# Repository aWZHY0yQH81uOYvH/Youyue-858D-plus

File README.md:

Youyue-858D-plus
================

Custom firmware and adapter PCB for the Youyue 858D+ with MK1841D3 stock MCU

This board and firmware is designed only for the ATmega328*PB* because it makes use of its extra port E I/O.

This repo includes a PCB that contains all the mods I could find:
* wguibas's MK1841D3 to AVR pinout adapting
* madworm's fancy fan speed commutation sensing
* RaiHei's buzzer
* Gabse's max fan speed cooldown
* 4 buttons for recalling preset temperatures
* Some extra I/O breakout for more hacking

Order the parts and PCB in the PCB folder. Then, use [this instructable](https://www.instructables.com/id/858D-SMD-Hot-Ait-Reflow-Station-Hack/) as a general guide. Add some buttons to the front panel for the presets.

There is a 'user manual' of sorts in the 'Docs' folder.

Some videos showing the progress from 'stock firmware' with massive temperature overshoot
towards almost no overshoot at all.

https://www.youtube.com/playlist?list=PLONcxJMOrdyeYuEgM6qhCllZelN6gPjrT

Please note:

Although this device looks very much like ones sold by 'Atten' and others, the innards
are not necessarily the same. The heater / wand are probably the same, but I know that
e.g. the 'Atten 858D' uses a different mainboard with a different brand microcontroller.

Naturally, this firmware will only work 'as is' for the exact mcu / mainboard combination I have.
Please see the 'Docs' folder for schematic and PCB photos.

Compiling/Development
=====================
Since this version of the firmware uses the PB variant of the chip, you need to use the makefile. You may need to adjust `ISP_PROG` and `AVRDUDE_ARD_PROGRAMMER` in the makefile depending on what programmer you have.
* Do `make` to just compile the project.
* Do `make ispload` to compile and upload the project.
* If you don't want to edit the firmware, you can just follow the instructions in the binaries folder to upload without compiling.

---

Safety information / disclaimer:
================================

Making any modifications to this device may cause you irreversible physical harm or worse.
You do this at your own risk. 

There is a significant risk of lethal electrical shock, so if you still insist of doing so, make sure to
ALWAYS UNPLUG THE MAINS CABLE before dismantling the device. Check repeatedly.

If you have an isolation transformer - do use it.

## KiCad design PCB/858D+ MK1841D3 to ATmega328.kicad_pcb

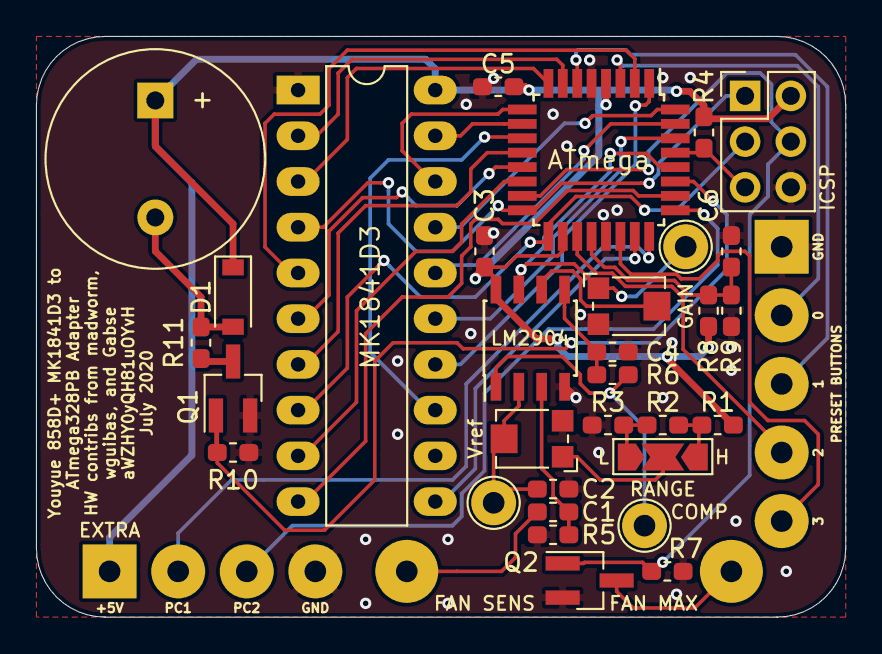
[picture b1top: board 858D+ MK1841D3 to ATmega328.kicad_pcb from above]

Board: 2 copper layers, 45.0 x 32.3 mm, 35 parts (0 on the bottom side), 42 nets.

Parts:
BZ1: Buzzer; Buzzer_12x9.5RM6.5
C1, C2, C3, C5, C6: 100n; C_0603_1608Metric_Pad1.05x0.95mm_HandSolder
C4: 1µ; C_0603_1608Metric_Pad1.05x0.95mm_HandSolder
D1: D_Small; D_SOD-123
J1: ISENSE; SolderWirePad_1x01_Drill1.2mm
J2: ICSP; PinHeader_2x03_P2.54mm_Vertical
J3: MK1841D3; DIP-20_W7.62mm_LongPads
J4: Extra; SolderWirePad_1x04_P3.81mm_Drill1.2mm
J5: FAN_MAX_SPEED; SolderWirePad_1x01_Drill1.2mm
JP1: SolderJumper_3_Open; SolderJumper-3_P2.0mm_Open_TrianglePad1.0x1.5mm
Q1, Q2: 2N7002; SOT-23_Handsoldering
R1, R4, R7, R8, R9, R10: 10k; R_0603_1608Metric_Pad1.05x0.95mm_HandSolder
R2, R3: 390; R_0603_1608Metric_Pad1.05x0.95mm_HandSolder
R5: 1M; R_0603_1608Metric_Pad1.05x0.95mm_HandSolder
R6: 100k; R_0603_1608Metric_Pad1.05x0.95mm_HandSolder
R11: 220; R_0603_1608Metric_Pad1.05x0.95mm_HandSolder
RV1, RV2: 10k; Potentiometer_Bourns_TC33X_Vertical
SW1: SW_Push_4x; SolderWirePad_1x05_P3.81mm_Drill1.2mm
TP1: Vref; TestPoint_THTPad_D2.5mm_Drill1.2mm
TP2: COMP_ADJ; TestPoint_THTPad_D2.5mm_Drill1.2mm
TP3: FAN_SPEED; TestPoint_THTPad_D2.5mm_Drill1.2mm
U1: LM2904; SOIC-8_3.9x4.9mm_P1.27mm
U2: ATmega328PB-AU; TQFP-32_7x7mm_P0.8mm

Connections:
+5V: BZ1.1, C3.1, C5.2, D1.1, J2.2, J3.20, J4.1, R1.1, R4.1, R8.1, U1.8, U2.4, U2.18
/PB0: J3.7, U2.12
/PB1: J3.6, U2.13
/PB2: J3.9, U2.14
/PB3: J2.4, Q2.1, R7.1, U2.15
/PB4: J2.1, J3.4, U2.16
/PB5: J2.3, J3.8, U2.17
/PB6: J3.2, U2.7
/PB7: J3.3, U2.8
/PC0: J3.11, U2.23
/PC1: J4.2, U2.24
/PC2: J4.3, U2.25
/PC3: J3.10, U2.26
/PC4: Q1.1, R10.1, U2.27
/PC5: RV2.1, TP3.1, U1.7, U2.28
/PD0: J3.15, U2.30
/PD1: J3.16, U2.31
/PD2: J3.17, U2.32
/PD3: J3.14, U2.1
/PD4: J3.5, U2.2
/PD5: J3.18, U2.9
/PD6: J3.19, U2.10
/PD7: J3.13, U2.11
/PE0: SW1.2, U2.3
/PE1: SW1.3, U2.6
/PE2: SW1.4, U2.19
/PE3: SW1.5, U2.22
/RESET: J2.5, R4.2, U2.29
GND: C2.2, C3.2, C4.2, C5.1, C6.2, J2.6, J3.1, J4.4, Q1.2, Q2.2, R3.2, R5.2, R7.2, R9.2, R10.2, RV1.3, RV2.3, SW1.1, U1.4, U2.5, U2.21
unnamed: BZ1.2, D1.2, R11.1
unnamed: C1.1, R5.1, U1.3
unnamed: C1.2, J1.1
unnamed: C2.1, RV1.2, TP1.1, U1.2
unnamed: C4.1, R6.1, U1.5
unnamed: C6.1, R8.2, R9.1, U2.20
unnamed: J5.1, Q2.3
unnamed: JP1.1, R2.2, R3.1
unnamed: JP1.2, RV1.1
unnamed: JP1.3, R1.2, R2.1
unnamed: Q1.3, R11.2
unnamed: R6.2, TP2.1, U1.1
unnamed: RV2.2, U1.6

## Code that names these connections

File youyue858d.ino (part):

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#define FW_MINOR_V_A 4
#define FW_MINOR_V_B 9
/*
 * PC5: FAN-speed (A5 in Arduino lingo) (OK)
 * PC3: TIP122.base --> FAN (OK)
 * PC2: fan-current-sense mod (OPTIONAL) - see Docs folder
 * PC0: ADC <-- amplif. thermo couple voltage (A0 in Arduino lingo) (OK)
 * #21: AREF <--- about 2.5V as analog reference for ADC
 * PB1: opto-triac driver !! THIS IS DANGEROUS TO USE !! (OK)
 * PB3: FAN to maximum output (OPTIONAL)
 *
 * PB0: 7-seg digit 0 [common Anode] (OK) 
 * PB7: 7-seg digit 1 [common Anode] (OK)
 * PB6: 7-seg digit 2 [common Anode] (OK)
 *
 * PD0: 7-seg top (OK)
 * PD1: 7-seg bottom left (OK)
 * PD2: 7-seg bottom (OK)
 * PD3: 7-seg top left (OK)
 * PD4: 7-seg dot (OK)
 * PD5: 7-seg bottom right (OK)
 * PD6: 7-seg middle (OK)
 * PD7: 7-seg top right (OK)
 *
 * PB5: SW1 (button1) (OK)
 * PB2: SW2 (button2) (OK)
 * PB4: reed switch (wand cradle sensor) (OK)
 *
 * PE0: Preset 1
 * PE1: Preset 2
 * PE2: Preset 3
 * PE3: Preset 4
 *
 */

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void setup_858D(void)
{
	HEATER_OFF;
	DDRB |= _BV(PB1);	// set as output for TRIAC control

	DDRB &= ~(_BV(PB5) | _BV(PB2));	// set as inputs (switches)
	PORTB |= (_BV(PB5) | _BV(PB2));	// pull-up on

	DDRB &= ~_BV(PB4);	// set as input (reed sensor)
	PORTB |= _BV(PB4);	// pull-up on

	FAN_OFF;
	DDRC |= _BV(PC3);	// set as output (FAN control)

	DDRD |= 0xFF;		// all as outputs (7-seg segments)
	DDRB |= (_BV(PB0) | _BV(PB6) | _BV(PB7));	// 7-seg digits 1,2,3

	DDRB |= _BV(PB3); // set FAN_MAX as output
	
	DDRE = 0; // Buttons
	PORTE = 0b00001111; // Pullups


#ifdef CURRENT_SENSE_MOD
	DDRC &= ~_BV(PC2);	// set as input
#endif

	setup_timer1_ctc();	// needed for background display refresh
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
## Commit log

2020-09-25 added preset buttons n stuff

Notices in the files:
youyue858d.ino:
License: GNU GPL v2
